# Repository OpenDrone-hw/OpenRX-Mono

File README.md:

# OpenRX Mono

Open-source dual-band (868/915 MHz and 2.4 GHz) ExpressLRS radio control receiver
module with telemetry, for any radio-controlled build: cars, boats, robots and
aircraft. OpenRX Mono uses an ESP32-C3 and one LR1121 with a 2.4 GHz PA/LNA,
sub-GHz matching network and a shared U.FL antenna interface.
It passes the received channels over serial (CRSF) on its RX and TX pads to a
controller, for example a flight controller or a vehicle or robot controller.

## Specifications

| | |
|---|---|
| Band | 2.4 GHz and sub-GHz |
| Radio | LR1121 |
| Antenna | U.FL |
| Telemetry power | Up to 22 dBm (158 mW) |
| Protocol | CRSF |
| MCU | ESP32-C3 |
| Input | 5 V pad |
| Firmware | ExpressLRS |
| Flashing | Betaflight passthrough or Wi-Fi |
| Dimensions | 10.0 x 17.3 mm |
| PCB | 6-layer, 1.0 mm |

Technical write-up, part list and layout constraints: [AGENTS.md](AGENTS.md).

## In the line

What pairs with what, and what is available:
[opendrone.be](https://opendrone.be).

## Contributing

See [CONTRIBUTING.md](CONTRIBUTING.md).

## License

Hardware licensed under [CERN-OHL-S-2.0](https://ohwr.org/cern_ohl_s_v2.txt),
see [LICENSE](LICENSE).

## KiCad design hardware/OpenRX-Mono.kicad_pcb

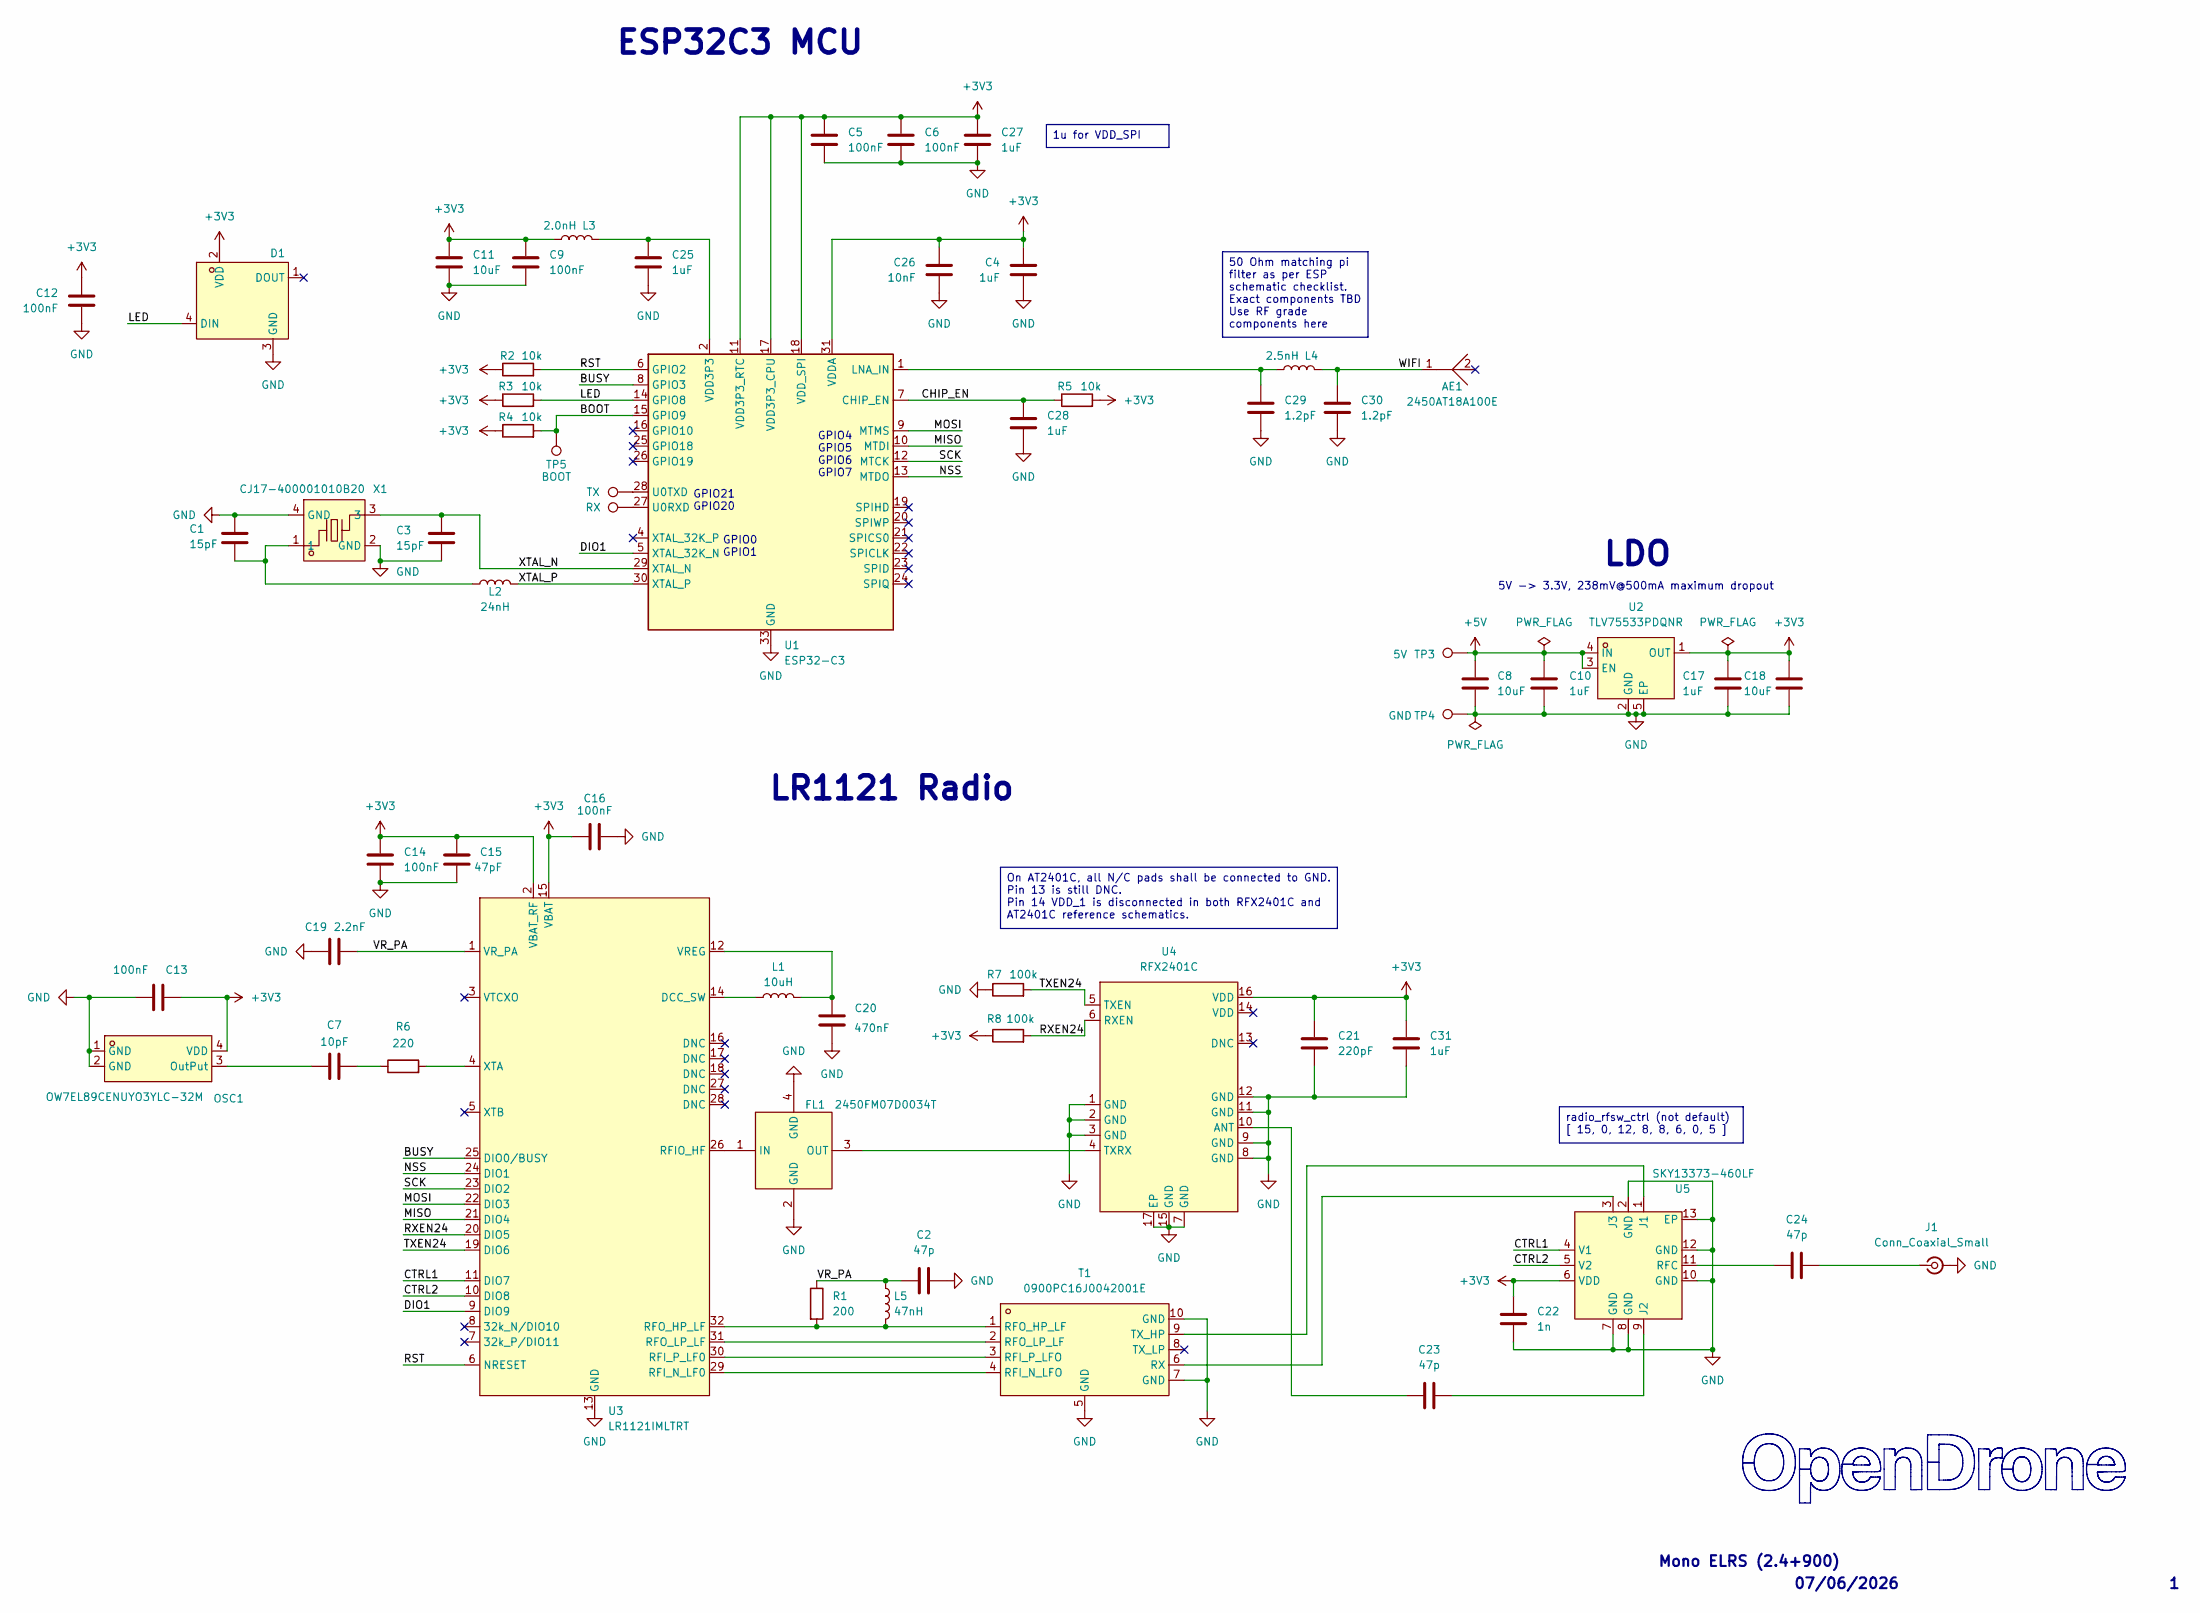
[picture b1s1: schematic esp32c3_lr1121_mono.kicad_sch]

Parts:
AE1: 2450AT18A100E; ANT-SMD_L3.2-W1.6; MPN 2450AT18A100E; LCSC Part C89334
C1, C3: 15pF; C_0201_0603Metric; MPN GRM0335C1H150JA01D; LCSC C85891
C2, C23, C24: 47p; C_0201_0603Metric; MPN GRM0335C1H470JA01D; LCSC C85908
C4, C10, C17, C25, C27, C28, C31: 1uF; C_0201_0603Metric; MPN GRM033R61A105ME44D; LCSC C76935
C5, C6, C9, C12, C13, C14, C16: 100nF; C_0201_0603Metric; MPN GRM033R61E104KE14D; LCSC C76939
C7: 10pF; C_0201_0603Metric; MPN GRM0335C1H100FA01D; LCSC C384956
C8, C18: 10uF; C_0402_1005Metric; MPN CL05A106MQ5NUNC; LCSC C15525
C11: 10uF; C_0402_1005Metric; MPN GRM155R60J106ME44D; LCSC C76991
C15: 47pF; C_0201_0603Metric; MPN GRM0335C1H470JA01D; LCSC C85908
C19: 2.2nF; C_0201_0603Metric; MPN GRM033R71E222KA12D; LCSC C161488
C20: 470nF; C_0201_0603Metric; MPN GRM033R60J474KE90D; LCSC C85926
C21: 220pF; C_0201_0603Metric; MPN GRM0335C1E221JA01D; LCSC C907939
C22: 1n; C_0201_0603Metric; MPN GRM033R71H102KA12D; LCSC C85934
C26: 10nF; C_0201_0603Metric; MPN GRM033R61A103KA01J; LCSC C2168164
C29, C30: 1.2pF; C_0201_0603Metric; MPN GRM0335C1H1R2BA01D; LCSC C85895
D1: XL-1010RGBC-WS2812B; LED-SMD_4P-L1.0-W1.0-TL_XL-1010RGBC-WS2812B; MPN XL-1010RGBC-2812B; LCSC C5349953
FL1: 2450FM07D0034T; FILTER-SMD_4P-L1.0-W0.5-L; MPN 2450FM07D0034T; LCSC Part_1 C2651081
J1: Conn_Coaxial_Small; U.FL_Hirose_U.FL-R-SMT-1_Vertical; MPN U.FL-R-SMT-1(80); LCSC C88374
L1: 10uH; L_0603_1608Metric; MPN MLZ1608N100LT000; LCSC C194437
L2: 24nH; L_0201_0603Metric; MPN LQP03TN24NH02D; LCSC C206441
L3: 2.0nH; L_0201_0603Metric; MPN LQP03TN2N0B02D; LCSC C86125
L4: 2.5nH; L_0201_0603Metric; MPN LQP03TN2N5C02D; LCSC C206435
L5: 47nH; L_0402_1005Metric; MPN LQW15AN47NJ00D; LCSC C192855
OSC1: OW7EL89CENUYO3YLC-32M; OSC-SMD_4P-L2.0-W1.6-BL_TXC_7Z; MPN OW7EL89CENUYO3YLC-32M; LCSC C22381772
R1: 200; R_0201_0603Metric; MPN RC0201FR-07200RL; LCSC C274337
R2, R3, R4, R5: 10k; R_0201_0603Metric; MPN RC0201FR-0710KL; LCSC C106225
R6: 220; R_0201_0603Metric; MPN ERJ-1GNF2200C; LCSC C2074788
R7, R8: 100k; R_0201_0603Metric; MPN RC0201FR-07100KL; LCSC C106224
T1: 0900PC16J0042001E; FILTER-SMD_10P-L2.0-W1.6-BL; MPN 0900PC16J0042001E; LCSC C19842466
TP1: RX; SolderPad_1.2x2.0mm
TP2: TX; SolderPad_1.2x2.0mm
TP3: 5V; SolderPad_1.2x2.0mm
TP4: GND; SolderPad_1.2x2.0mm
TP5: BOOT; SolderPad_1.2x2.0mm
U1: ESP32-C3; QFN-32-1EP_5x5mm_P0.5mm_EP3.7x3.7mm; MPN ESP32-C3FH4; LCSC C2858491
U2: TLV75533PDQNR; X2SON-4_L1.0-W1.0-P0.65-TL-EP; MPN TLV75533PDQNR; LCSC Part C2861882
U3: LR1121IMLTRT; QFN-32-1EP_5x5mm_P0.5mm_EP3.7x3.7mm; MPN LR1121IMLTRT; LCSC C7498014
U4: RFX2401C; QFN-16_L3.0-W3.0-P0.50-BL-EP1.7; MPN RFX2401C; LCSC C19213
U5: SKY13373-460LF; QFN-12_EP_2x2_Pitch0.5mm; MPN SKY13373-460LF; LCSC C150853
X1: CJ17-400001010B20; CRYSTAL-SMD_4P-L1.6-W1.2-BL; MPN CJ17-400001010B20; LCSC Part C2875272

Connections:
+3V3: C4.1, C5.1, C6.1, C9.1, C11.1, C12.1, C13.2, C14.1, C15.1, C16.1, C17.1, C18.1, C21.1, C22.1, C26.1, C27.1, C31.1, D1.2 (VDD), L3.2, OSC1.4 (VDD), R2.1, R3.1, R4.1, R5.2, R8.1, U1.11 (VDD3P3_RTC), U1.17 (VDD3P3_CPU), U1.18 (VDD_SPI), U1.31 (VDDA), U1.32 (VDDA), U2.1 (OUT), U3.2 (VBAT_RF), U3.15 (VBAT), U4.16 (VDD), U5.6 (VDD)
+5V: C8.1, C10.1, TP3.1 (1_1), U2.3 (EN), U2.4 (IN)
/ESP32-C3 + LR1121 Mono/BOOT: R4.2, TP5.1 (1_1), U1.15 (GPIO9)
/ESP32-C3 + LR1121 Mono/BUSY: U1.8 (GPIO3), U3.25 (DIO0/BUSY)
/ESP32-C3 + LR1121 Mono/CHIP_EN: C28.1, R5.1, U1.7 (CHIP_EN)
/ESP32-C3 + LR1121 Mono/CTRL1: U3.11 (DIO7), U5.4 (V1)
/ESP32-C3 + LR1121 Mono/CTRL2: U3.10 (DIO8), U5.5 (V2)
/ESP32-C3 + LR1121 Mono/DIO1: U1.5 (XTAL_32K_N), U3.9 (DIO9)
/ESP32-C3 + LR1121 Mono/LED: D1.4 (DIN), R3.2, U1.14 (GPIO8)
/ESP32-C3 + LR1121 Mono/MISO: U1.10 (MTDI), U3.21 (DIO4)
/ESP32-C3 + LR1121 Mono/MOSI: U1.9 (MTMS), U3.22 (DIO3)
/ESP32-C3 + LR1121 Mono/NSS: U1.13 (MTDO), U3.24 (DIO1)
/ESP32-C3 + LR1121 Mono/RST: R2.2, U1.6 (GPIO2), U3.6 (NRESET)
/ESP32-C3 + LR1121 Mono/RXEN24: R8.2, U3.20 (DIO5), U4.6 (RXEN)
/ESP32-C3 + LR1121 Mono/SCK: U1.12 (MTCK), U3.23 (DIO2)
/ESP32-C3 + LR1121 Mono/TXEN24: R7.2, U3.19 (DIO6), U4.5 (TXEN)
/ESP32-C3 + LR1121 Mono/VR_PA: C2.1, C19.1, L5.1, R1.1, U3.1 (VR_PA)
/ESP32-C3 + LR1121 Mono/WIFI: AE1.1, C30.1, L4.1
/ESP32-C3 + LR1121 Mono/XTAL_N: C3.1, U1.29 (XTAL_N), X1.3
/ESP32-C3 + LR1121 Mono/XTAL_P: L2.2, U1.30 (XTAL_P)
GND: C1.2, C2.2, C3.2, C4.2, C5.2, C6.2, C8.2, C9.2, C10.2, C11.2, C12.2, C13.1, C14.2, C15.2, C16.2, C17.2, C18.2, C19.2, C20.1, C21.2, C22.2, C25.2, C26.2, C27.2, C28.2, C29.2, C30.2, C31.2, D1.3 (GND), FL1.2 (GND), FL1.4 (GND), J1.2 (Ext), OSC1.1 (GND), OSC1.2 (GND), R7.1, T1.5 (GND), T1.7 (GND), T1.10 (GND), TP4.1 (1_1), U1.33 (GND), U2.2 (GND), U2.5 (EP), U3.13 (GND), U3.33 (EP), U4.1 (GND), U4.2 (GND), U4.3 (GND), U4.7 (GND), U4.8 (GND), U4.9 (GND), U4.11 (GND), U4.12 (GND), U4.15 (GND), U4.17 (EP), U5.2 (GND), U5.7 (GND), U5.8 (GND), U5.10 (GND), U5.12 (GND), U5.13 (EP), X1.2 (GND), X1.4 (GND)
unnamed: C1.1, L2.1, X1.1
unnamed: C7.1, R6.1
unnamed: C25.1, L3.1, U1.2 (VDD3P3), U1.3 (VDD3P3)
unnamed: FL1.1 (IN), U3.26 (RFIO_HF)
unnamed: FL1.3 (OUT), U4.4 (TXRX)
unnamed: C24.2, J1.1 (In)
unnamed: C7.2, OSC1.3 (OutPut)
unnamed: T1.4 (RFI_N_LFO), U3.29 (RFI_N_LF0)
unnamed: T1.3 (RFI_P_LFO), U3.30 (RFI_P_LF0)
unnamed: L5.2, R1.2, T1.1 (RFO_HP_LF), U3.32 (RFO_HP_LF)
unnamed: T1.2 (RFO_LP_LF), U3.31 (RFO_LP_LF)
unnamed: T1.6 (RX), U5.3 (J3)
unnamed: T1.9 (TX_HP), U5.1 (J1)
unnamed: C29.1, L4.2, U1.1 (LNA_IN)
unnamed: TP1.1 (1_1), U1.27 (U0RXD)
unnamed: TP2.1 (1_1), U1.28 (U0TXD)
unnamed: L1.1, U3.14 (DCC_SW)
unnamed: C20.2, L1.2, U3.12 (VREG)
unnamed: R6.2, U3.4 (XTA)
unnamed: C23.1, U4.10 (ANT)
unnamed: C23.2, U5.9 (J2)
unnamed: C24.1, U5.11 (RFC)

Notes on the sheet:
GPIO0 GPIO1
LR1121 Radio
GPIO21 GPIO20
5V -> 3.3V, 238mV@500mA maximum dropout
07/06/2026
ESP32C3 MCU
LDO
Mono ELRS (2.4+900)
GPIO4 GPIO5 GPIO6 GPIO7
On AT2401C, all N/C pads shall be connected to GND. Pin 13 is still DNC. Pin 14 VDD_1 is disconnected in both RFX2401C and AT2401C reference schematics.
50 Ohm matching pi filter as per ESP schematic checklist. Exact components TBD Use RF grade components here
radio_rfsw_ctrl (not default) [ 15, 0, 12, 8, 8, 6, 0, 5 ]
1u for VDD_SPI

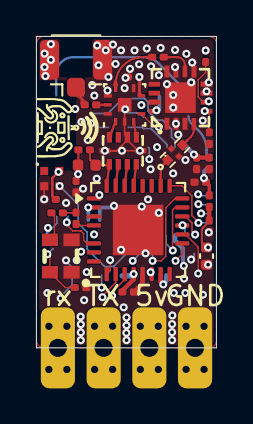
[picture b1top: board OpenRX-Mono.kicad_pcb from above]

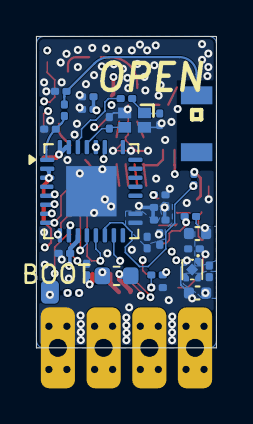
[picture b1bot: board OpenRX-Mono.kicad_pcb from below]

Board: 6 copper layers, 10.0 x 17.3 mm, 61 parts (30 on the bottom side), 43 nets.

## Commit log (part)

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2026-03-23 Consolidate docs: 1 README + KICAD_WORKFLOW + 1 DESIGN.md per receiver
    - Merge SCHEMATIC.md + BOM.md into single DESIGN.md per receiver
    - Delete OPENRX_ELRS_4_RECEIVER_PORTFOLIO.md (content integrated)
    - Delete REPO_AUDIT_2026-03-23.md (issues addressed)
    - Fold CORE_BOM into README.md architecture table
    - Rename KICAD_WORKFLOW_AND_ELRS_COMPATIBILITY.md to KICAD_WORKFLOW.md
    - Rewrite KICAD_WORKFLOW with step-by-step capture instructions
2026-03-23 Fix all DESIGN.md: RFX2401C, DEA LPF, LR1121 pinout, FEM control
    - Lite: remove L-match network, use DEA102700LT-6307A2 only
    - Nano: clarify DEA LPF path, mark 0.3pF as mandatory, SE2431L as EOL
    - 900: fix LR1121 RFSW description, confirm 4x4mm package
    - Dual: SE2431L→RFX2401C, FEM via LR1121 RFSW not MCU GPIO, BOM $9→$7.62
    - PWM: SE2431L→RFX2401C, DEA LPF + 0.3pF path, BOM $7.40→$6.02
    - Gemini: SE2431L→RFX2401C, fix FEM control model, BOM $10.84→$9.46
2026-03-23 Update all DESIGN.md: TLV75533 X2SON LDO, XL-1010 1x1mm LED
    - Lite/Nano/900/Dual: ME6211 SOT-23-5 → TLV75533PDQNR X2SON-4 (1x1mm)
    - Gemini: keeps AP2112K (600mA needed for dual radios)
    - PWM: keeps AMS1117 (needs >6V input range)
    - All: WS2812B-2020 → XL-1010RGBC-WS2812B (1x1mm)
    - Updated cap values for TLV755 (1uF local + 10uF bulk)
2026-03-23 Import DEA102700LT-6307A2 LPF into shared library (C574024)
2026-03-23 Import U.FL-R-SMT-1(80) UFL connector into shared library (C88374)
2026-03-23 Import Molex 479480001 tower ceramic antenna (C152351) for ELRS RF
2026-03-23 Add solder pad footprints: 1.0x1.5mm and 1.0x0.8mm compact
2026-03-23 Unify library tables, import RFX2401C, Lite schematic capture
    - All 6 projects now share OpenRX-Shared + OpenRX-Lite lib tables
    - Import RFX2401C (C19213) into shared library with 3D model path fix
    - OpenRX-Lite schematic: 0 ERC errors (captured in KiCad GUI)
    - Add .gitignore for .lck and .history files
2026-03-23 Import LR1121 (C7498014) and 32MHz TCXO (C22434888) into shared library
2026-03-23 Import Johanson 0900PC16J0042001E LR11xx sub-GHz IPD (C19842466) and LR1121 + 32MHz TCXO
2026-03-23 OpenRX-900: add all LCSC fields, fix 4.7uF to 0402
    - C20 (4.7uF): C23733, footprint fixed from 0201 to 0402
    - R5/R6/R7 (100k): C25741, RFSW pull-downs
    - L1 (10uH): C1035, 0603 DC-DC inductor
    - U4 (LR1121): C7498014
    - U5 (32MHz TCXO): C22434888
    - T1 (Johanson IPD): C19842466
2026-03-23 Fix Gemini crystal load caps to 18pF (C62164), matching Lite and Mono
2026-03-23 Repo cleanup: remove ERC reports, lock files, backup dirs, fix gitignore
2026-03-23 Add LCSC C430052 for 24nH XTAL_P inductor on Mono
    Mono L2 (24nH 0201) was missing LCSC field.
    Lite still needs 24nH inductor added in KiCad GUI.
    Gemini is parked — still a Mono copy, not yet dual-radio.
2026-03-23 OpenRX-Gemini: dual LR1121 schematic complete, 0 ERC errors
    - Radio 1 (U4): sub-GHz via Johanson IPD → JP1 UFL
    - Radio 2 (U9): 2.4GHz via RFX2401C (U10) → DEA (USB2) → JP3 UFL
    - Shared SPI bus (SCK/MISO/MOSI), separate NSS/IRQ/BUSY/RST per radio
    - Radio 2 control: GPIO10=NSS2, GPIO9=IRQ2, GPIO1=BUSY2, GPIO0=RST2
    - FEM driven by Radio 2 RFSW (DIO5→RXEN, DIO6→TXEN)
    - Radio 1 DIO5/DIO6 have 100k pull-downs (disconnected from FEM)
2026-03-23 Add SolderPad_1.2x2.0mm with 25% rounded corners, 2.0mm pitch standard
2026-03-23 Swap all solder pads to 1.2x2.0mm rounded (25%) across Lite, Mono, Gemini
2026-03-23 Swap 32MHz TCXO to smaller 2016 package (C22381772)
    OW2EL89 (3225, 3.2x2.5mm) → OW7EL89 (2016, 2.0x1.6mm)
    Same YXC family, same pinout, same specs. Saves 1.2x0.9mm per TCXO.
    Affects Mono (1x) and Gemini (2x).
2026-03-23 Import SKY13588-460LF SP3T RF switch (C2151906) into shared library
2026-03-23 Final topology: Mono + Gemini netlist with SKY13588 RF switch
    - SKY13588-460LF imported into shared library
    - Complete netlist for Mono (1×LR1121 + SKY13588 + Johanson IPD + DEA LPF → 1 UFL)
    - Gemini = 2× Mono RF chains + ESP32-C3 True Diversity GPIO mapping
    - GPIO maps match official ELRS Generic C3 LR1121 and True Diversity targets
    - Routing notes for RF paths included
    - Mono needs complete GPIO rewire to match ELRS target
2026-03-23 FINAL_NETLIST v3: SKY13588 as band combiner, RFX2401C kept for 100mW
    Based on RadioMaster XR4 teardown analysis:
    - SKY13588 serves as both sub-GHz path switch AND band combiner
    - Johanson IPD in direct-tie mode (RX/TX_LP/TX_HP joined) → SKY13588 J1
    - 2.4GHz: RFIO_HF → DEA LPF → RFX2401C → SKY13588 J2
    - SKY13588 RFC → DC block → UFL → dual-band antenna
    - RFX2401C kept for 100mW market parity
2026-03-23 Mono schematic v4: complete RF chain verified
    Verified netlist:
    - LR1121 → IPD (direct-tie, pins 6+8+9 joined) → SKY13588 J1 ✓
    - LR1121 RFIO_HF → DEA LPF → RFX2401C TXRX ✓
    - RFX2401C ANT → 0.3pF shunt → SKY13588 J2 ✓
    - SKY13588 RFC → UFL ✓
    - DIO7→V1, DIO8→V2 (band select) ✓
2026-03-24 Gemini: copy Mono schematic as base for dual-radio build
2026-03-24 Gemini: copy Mono schematic + PCB as starting point
2026-03-24 Copy Gemini PCB layout to Mono
2026-03-24 Apply JLCPCB 6-layer advanced DRC rules to Mono and Gemini
    Rules applied:
    - Min clearance: 0.09mm (3.5mil)
    - Min track width: 0.09mm (3.5mil)
    - Min via diameter: 0.25mm
    - Min via drill: 0.15mm
    - Min annular ring: 0.05mm
2026-03-24 Repo cleanup: final state for handoff
    - Clean README with architecture, BOM, CE notes, status
    - Remove dated analysis files (absorbed into FINAL_NETLIST + KICAD_WORKFLOW)
    - Remove stale OpenRX-Dual (archived), ERC reports, backups, prl files
    - Updated .gitignore for .kicad_dru, production backups
    - CERN-OHL-S v2 license confirmed
    - 3 active projects: Lite, Mono, Gemini
2026-03-24 Revise target prices in receiver specifications
    Updated target prices for Lite, Mono, and Gemini models.
2026-03-24 Consolidate active RX docs and shared project metadata
2026-04-21 initial routing for all
2026-04-27 final route
2026-04-28 Set via netclass + dimension defaults to 0.3/0.2mm on all 4 boards
2026-04-28 switch to 0.2mm vias
2026-04-28 gitignore JLC per-quote BOM markdown drops
2026-05-08 OpenRX Lite (UFL + molex)
2026-05-13 fab and placement output for combined order
2026-06-07 annotate
